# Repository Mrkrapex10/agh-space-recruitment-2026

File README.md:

# AGH Space Systems – zadania rekrutacyjne 2026 (Elektronika)

Rozwiązane zadania:

| Zadanie | Co to jest | Gdzie |
|---|---|---|
| **1.1 Hardware** | Moduł przetwornicy 24 V → 5 V / 3 A na AP63300, płytka 30 × 30 mm, 4 × M2 | `hardware/` |
| **1.2 Hardware** | Projekt systemu: diagram i notatka dla grzałek, pompy, belek tensometrycznych, termopar, serw i paska WS2812B (zasilanie 24 V + CAN FD) | `hardware/system_1_2/` |

## Hardware (zadanie 1.1)

- Opis, schemat, rysunki płytki i lista części z numerami MPN: [`hardware/Zadanie_1_1_opis.pdf`](hardware/Zadanie_1_1_opis.pdf)
- Projekt KiCad (wersja 10.0.7): otwórz `hardware/ap63300_buck/ap63300_buck.kicad_pro`.
  Biblioteki (symbol AP63300 i footprint cewki Bourns SRP5030HMT) leżą w tym samym folderze projektu, więc nic nie trzeba doinstalowywać.
- Pliki PDF ze schematu wyeksportowane z KiCada: `hardware/ap63300_buck/export/`.

## Hardware (zadanie 1.2)

- Diagram systemu (strona 1, format A3) i notatka z założeniami, bilansem prądów, doborem układów i złączy oraz uwagami do projektu PCB (strony 2–5):
  [`hardware/system_1_2/Zadanie_1_2_diagram_i_notatka.pdf`](hardware/system_1_2/Zadanie_1_2_diagram_i_notatka.pdf)
- Noty katalogowe wybranych układów i serii złączy: [`hardware/system_1_2/datasheets/`](hardware/system_1_2/datasheets/) (lista plików i źródeł w `README.md` w tym folderze).

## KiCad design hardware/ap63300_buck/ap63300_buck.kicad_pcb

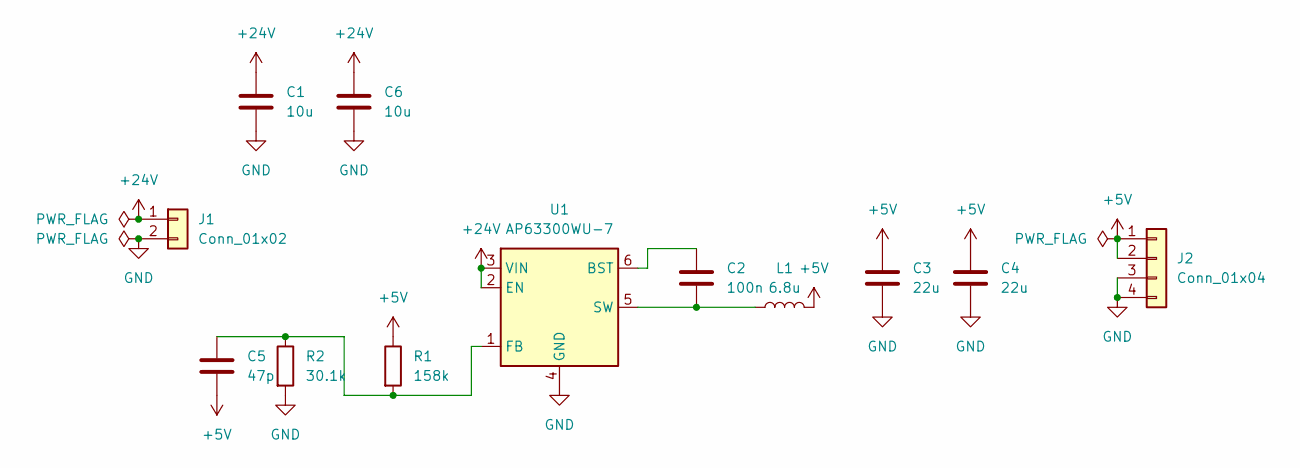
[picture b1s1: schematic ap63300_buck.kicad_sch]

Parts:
C1, C6: 10u; C_1206_3216Metric; MPN CL31B106KBHNNNE
C2: 100n; C_0603_1608Metric; MPN GRM188R71H104KA93D
C3, C4: 22u; C_0805_2012Metric; MPN GRM21BR61C226ME44L
C5: 47p; C_0603_1608Metric; MPN GRM1885C1H470JA01D
J1: Conn_01x02; PinHeader_1x02_P2.54mm_Vertical; MPN M20-9990245
J2: Conn_01x04; PinHeader_1x04_P2.54mm_Vertical; MPN M20-9990445
L1: 6.8u; L_Bourns_SRP5030HMT; MPN SRP5030HMT-6R8M
R1: 158k; R_0603_1608Metric; MPN RC0603FR-07158KL
R2: 30.1k; R_0603_1608Metric; MPN RC0603FR-0730K1L
U1: AP63300WU-7; TSOT-23-6; MPN AP63300WU-7

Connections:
+5V: C3.1, C4.1, C5.2, J2.1, J2.2, L1.2, R1.1
+24V: C1.1, C6.1, J1.1, U1.2 (EN), U1.3 (VIN)
GND: C1.2, C3.2, C4.2, C6.2, J1.2, J2.3, J2.4, R2.2, U1.4 (GND)
unnamed: C2.1, U1.6 (BST)
unnamed: C5.1, R1.2, R2.1, U1.1 (FB)
unnamed: C2.2, L1.1, U1.5 (SW)

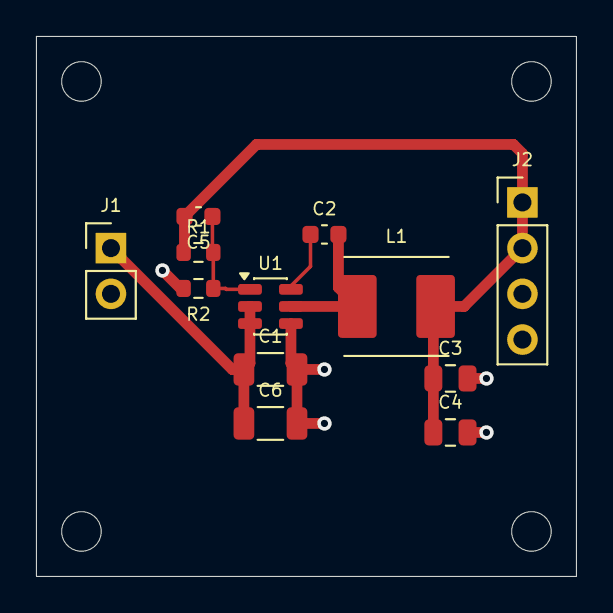
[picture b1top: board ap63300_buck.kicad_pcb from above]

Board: 2 copper layers, 30.0 x 30.0 mm, 12 parts (0 on the bottom side), 6 nets.
